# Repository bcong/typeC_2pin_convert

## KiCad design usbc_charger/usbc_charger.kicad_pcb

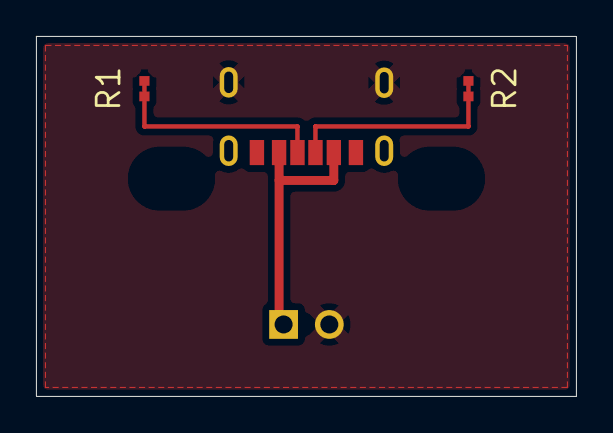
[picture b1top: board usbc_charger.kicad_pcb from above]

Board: 2 copper layers, 30.0 x 20.0 mm, 6 parts (0 on the bottom side), 4 nets.

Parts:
H1, H2: MountingHole; MountingHole_3.2mm_M3
J1: USB_C_6PIN; USB_C_Receptacle_6Pin_4Hole
J2: WF-XH2.54-2PZZ; PinHeader_1x02_P2.54mm_Vertical
R1, R2: 5.1k; R_0402

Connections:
CC1: J1.3, R1.1
CC2: J1.4, R2.1
GND: J1.1, J1.6, J1.M1, J1.M2, J1.M3, J1.M4, J2.2, R1.2, R2.2
VBUS: J1.2, J1.5, J2.1

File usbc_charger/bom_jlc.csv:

Comment,Designator,Footprint,LCSC Part #
5.1k,"R1,R2",Resistor_SMD:R_0402,C25905
USB_C_Receptacle,J1,Connector_USB:USB_C_Receptacle_6Pin_4Hole,C7507406
S2B-PH-SM4-TB,J2,Connector_JST:JST_PH_S2B-PH-SM4-TB_1x02-1MP_P2.00mm_Horiz,C295747
